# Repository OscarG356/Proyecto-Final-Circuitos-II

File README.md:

# Proyecto Final Circuitos II
En este repo se encuentran los archivos de EAGLE que tienen el diseño de la PCB utilizada para el proyecto final de circuitos II 2023-2. :)

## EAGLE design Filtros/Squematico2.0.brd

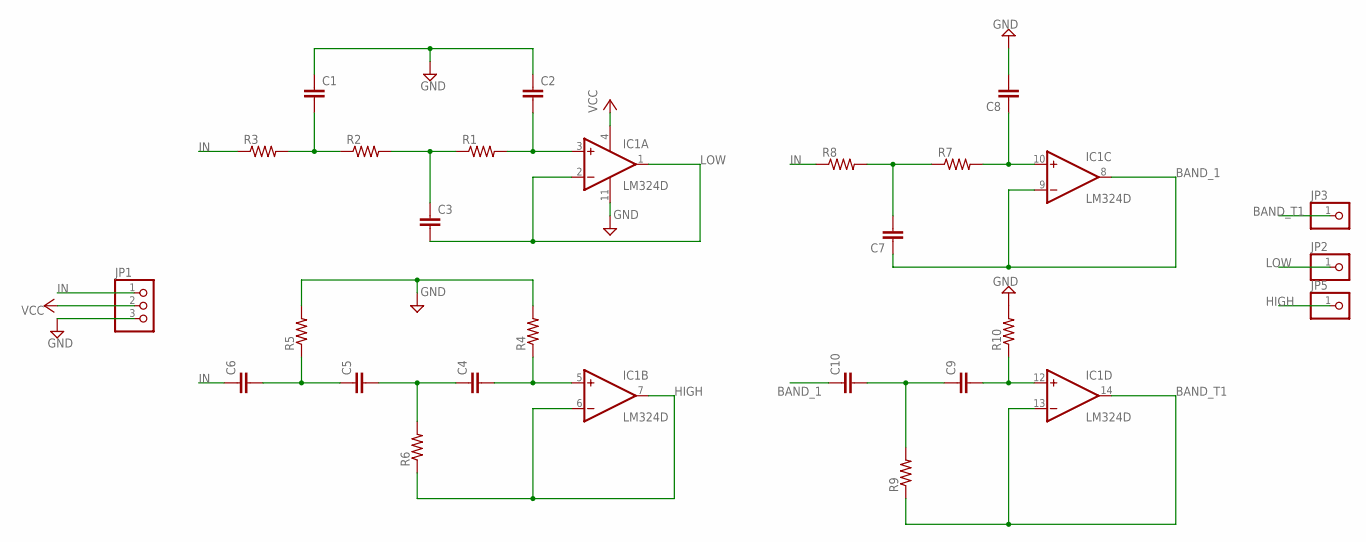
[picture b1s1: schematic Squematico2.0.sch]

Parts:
C1, C2, C3, C4, C5, C6, C7, C8, C9, C10: C-EU025-025X050; C025-025X050
IC1: LM324D; SO14
JP1: PINHD-1X3; 1X03
JP2, JP3, JP5: PINHD-1X1; 1X01
R1, R2, R3, R4, R5, R6, R7, R8, R9, R10: R-US_0204/7; 0204/7

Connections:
BAND_1: C7.1, C10.1, IC1.8 (OUT), IC1.9 (-IN)
BAND_T1: IC1.13 (-IN), IC1.14 (OUT), JP3.1, R9.1
GND: C1.1, C2.1, C8.2, IC1.11 (V-), JP1.3, R4.2, R5.2, R10.2
HIGH: IC1.6 (-IN), IC1.7 (OUT), JP5.1, R6.1
IN: C6.1, JP1.1, R3.1, R8.1
LOW: C3.2, IC1.1 (OUT), IC1.2 (-IN), JP2.1
unnamed: C2.2, IC1.3 (+IN), R1.2
unnamed: C3.1, R1.1, R2.2
unnamed: C1.2, R2.1, R3.2
unnamed: C4.2, IC1.5 (+IN), R4.1
unnamed: C4.1, C5.2, R6.2
unnamed: C5.1, C6.2, R5.1
unnamed: C7.2, R7.1, R8.2
unnamed: C8.1, IC1.10 (+IN), R7.2
unnamed: C9.2, IC1.12 (+IN), R10.1
unnamed: C9.1, C10.2, R9.2
VCC: IC1.4 (V+), JP1.2

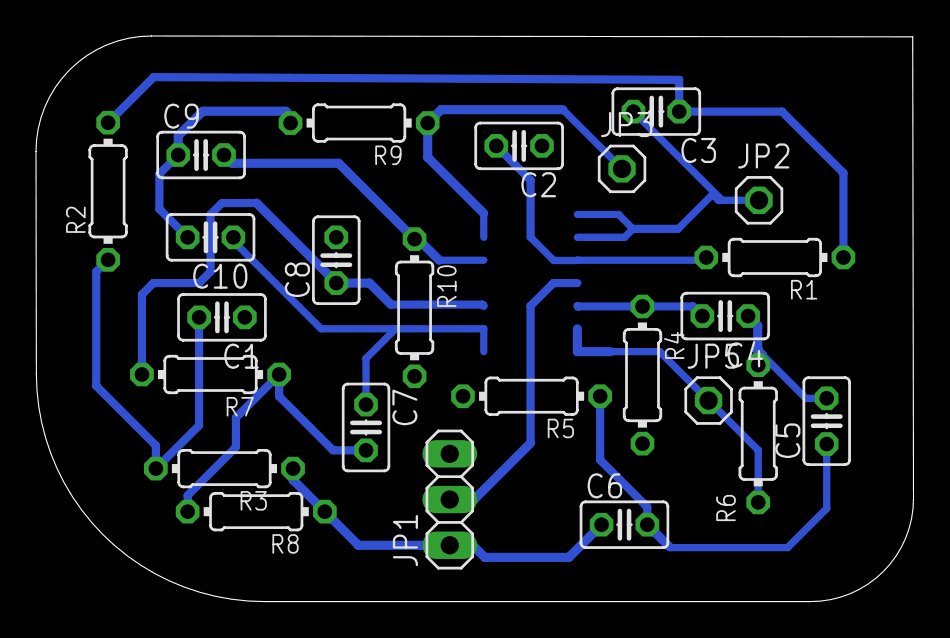
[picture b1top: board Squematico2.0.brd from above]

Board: 2 copper layers, 48.8 x 31.4 mm, 25 parts (1 on the bottom side), 17 nets.

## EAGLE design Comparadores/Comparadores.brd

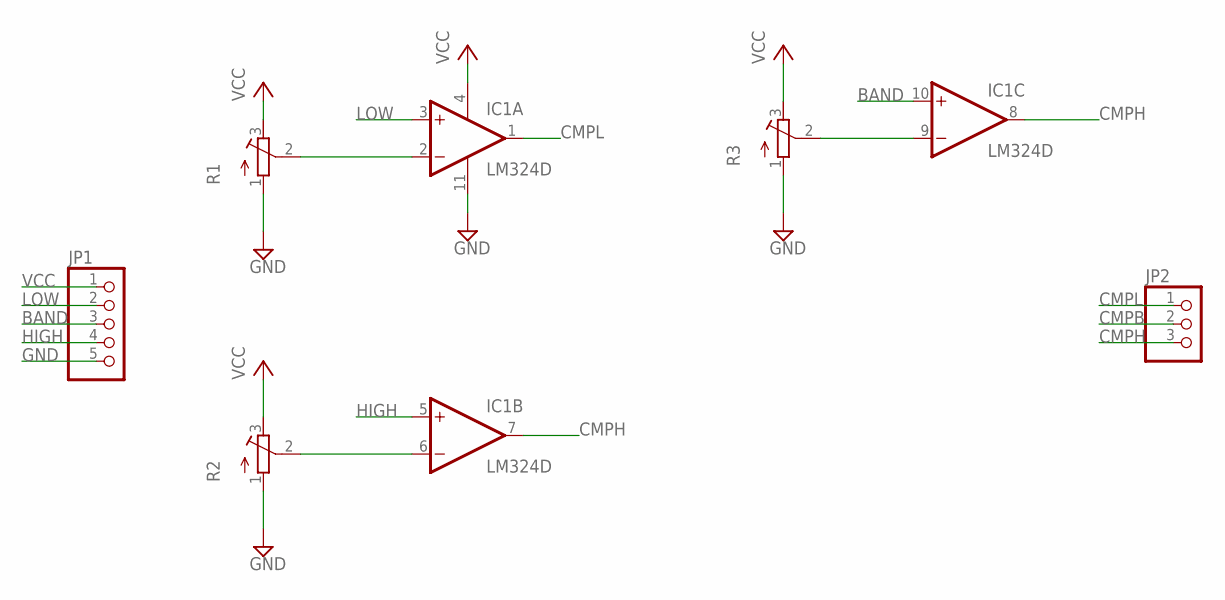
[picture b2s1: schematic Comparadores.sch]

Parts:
IC1: LM324D; SO14
JP1: PINHD-1X5; 1X05
JP2: PINHD-1X3; 1X03
R1, R2, R3: R-TRIMM64W; RTRIM64W

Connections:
BAND: IC1.10 (+IN), JP1.3
CMPB: JP2.2
CMPH: IC1.7 (OUT), IC1.8 (OUT), JP2.3
CMPL: IC1.1 (OUT), JP2.1
GND: IC1.11 (V-), JP1.5, R1.1 (A), R2.1 (A), R3.1 (A)
HIGH: IC1.5 (+IN), JP1.4
LOW: IC1.3 (+IN), JP1.2
unnamed: IC1.2 (-IN), R1.2 (S)
unnamed: IC1.6 (-IN), R2.2 (S)
unnamed: IC1.9 (-IN), R3.2 (S)
VCC: IC1.4 (V+), JP1.1, R1.3 (E), R2.3 (E), R3.3 (E)

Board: 2 copper layers, 6 parts (0 on the bottom side), 10 nets, no tracks yet.

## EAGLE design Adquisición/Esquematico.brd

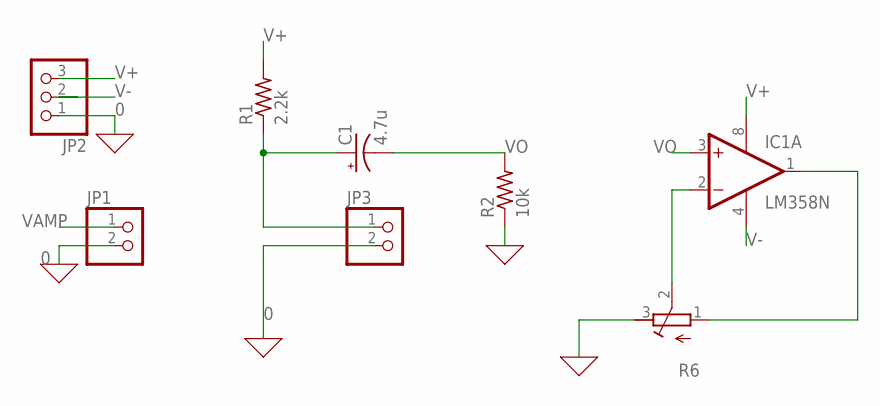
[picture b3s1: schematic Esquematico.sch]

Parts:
C1: 4.7u; E3,5-8
IC1: LM358N; DIL08
JP1, JP3: PINHD-1X2; 1X02
JP2: PINHD-1X3; 1X03
R1: 2.2k; 0207/10
R2: 10k; 0207/10
R6: R-TRIMM64W; RTRIM64W

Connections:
0: JP1.2, JP2.1, JP3.2, R2.1, R6.3 (E)
unnamed: C1.+, JP3.1, R1.1
unnamed: IC1.2 (-IN), R6.2 (S)
V+: IC1.8 (V+), JP2.3, R1.2
V-: IC1.4 (V-), JP2.2
VAMP: IC1.1 (OUT), JP1.1, R6.1 (A)
VO: C1.-, IC1.3 (+IN), R2.2

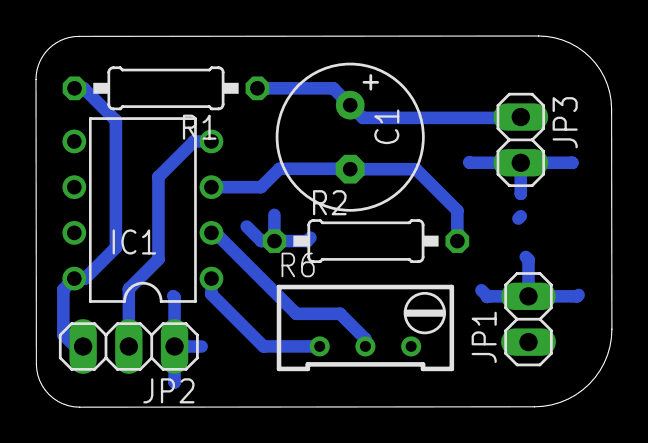
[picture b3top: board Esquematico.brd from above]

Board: 2 copper layers, 32.0 x 20.6 mm, 8 parts (0 on the bottom side), 7 nets.

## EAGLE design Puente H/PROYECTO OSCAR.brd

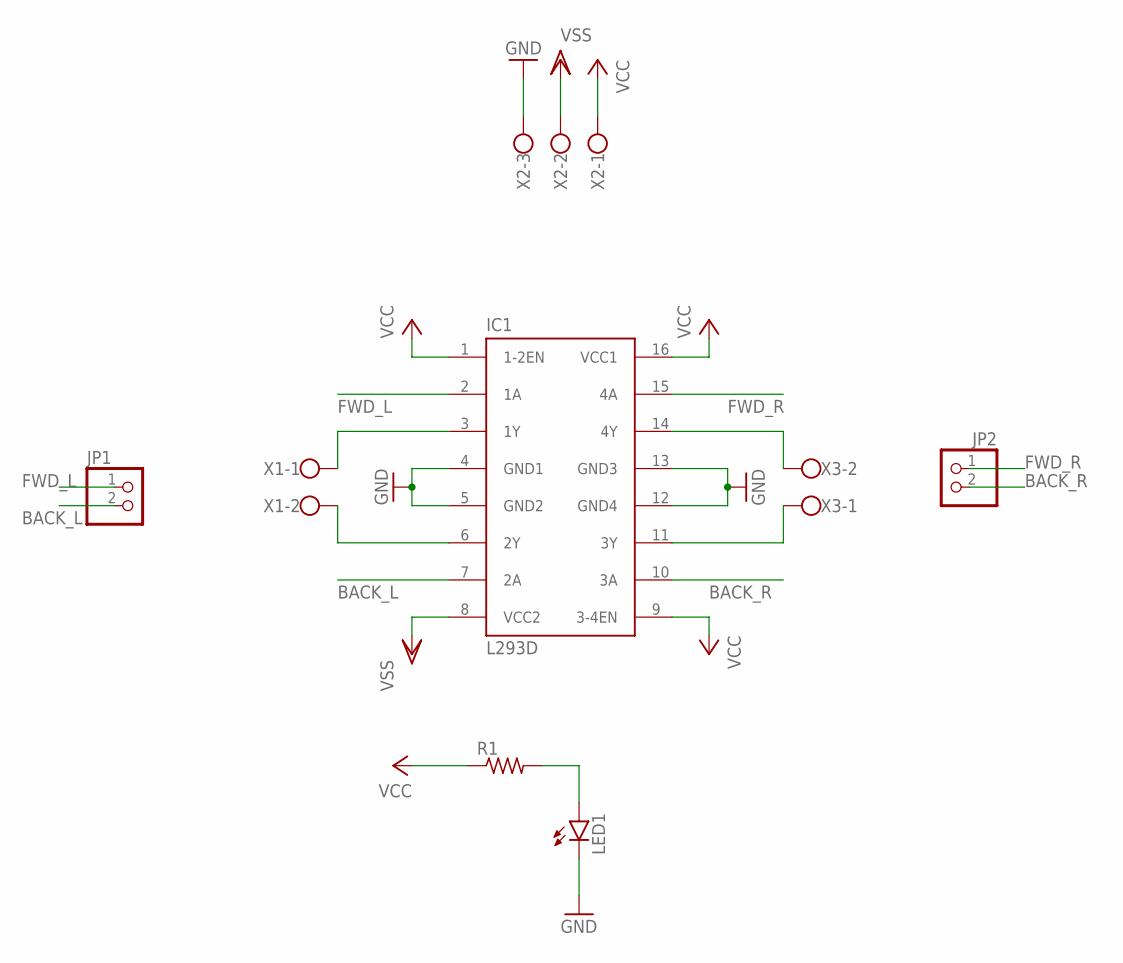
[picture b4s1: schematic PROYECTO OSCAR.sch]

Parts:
IC1: L293D; DIL16
JP1, JP2: PINHD-1X2; 1X02
LED1: LED5MM
R1: R-US_0204/7; 0204/7
X1, X3: W237-102
X2: W237-103

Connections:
BACK_L: IC1.7 (2A), JP1.2
BACK_R: IC1.10 (3A), JP2.2
FWD_L: IC1.2 (1A), JP1.1
FWD_R: IC1.15 (4A), JP2.1
GND: IC1.4 (GND1), IC1.5 (GND2), IC1.12 (GND4), IC1.13 (GND3), LED1.K (C), X2.3
unnamed: LED1.A, R1.2
unnamed: IC1.3 (1Y), X1.1
unnamed: IC1.6 (2Y), X1.2
unnamed: IC1.14 (4Y), X3.2
unnamed: IC1.11 (3Y), X3.1
VCC: IC1.1 (1-2EN), IC1.9 (3-4EN), IC1.16 (VCC1), R1.1, X2.1
VSS: IC1.8 (VCC2), X2.2

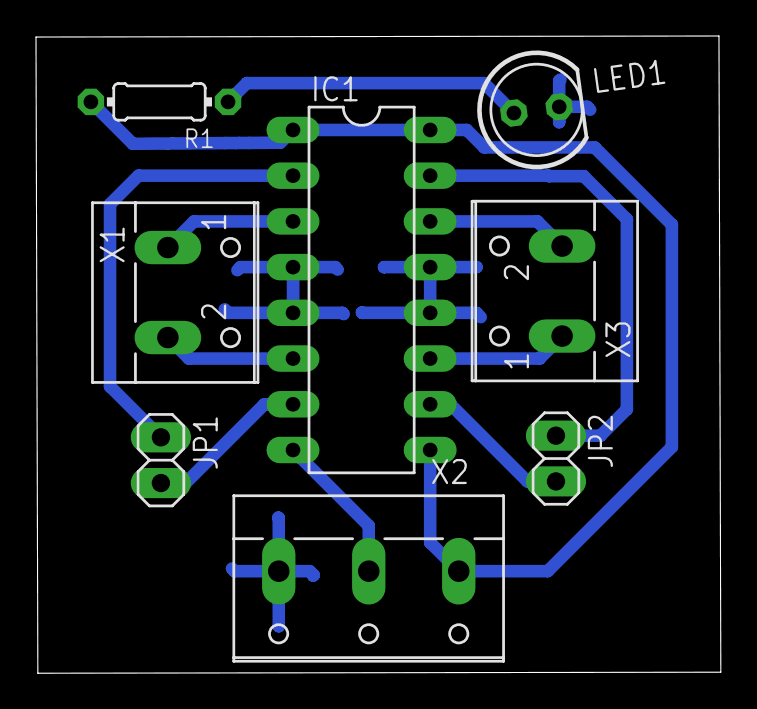
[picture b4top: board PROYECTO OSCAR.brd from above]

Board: 2 copper layers, 38.0 x 35.4 mm, 8 parts (0 on the bottom side), 12 nets.

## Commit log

2023-10-13 Sistema de adquisición completo
2023-11-06 Se añade la etapa de control y el código arduino para decodificar la señal
2023-11-16 Se añade el puente H, y los gerber para las PCBs anteriores
2023-11-16 Se añaden filtros sin contectar
2023-11-17 Se agregan pistas para los filtros y se crean los comparadores
2023-11-22 Se agregan conexiones y archivos de configuración CNC
